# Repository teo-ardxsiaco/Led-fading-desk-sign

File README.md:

# Led-fading-desk-sign
This project started as a heartfelt, custom-made desk gift for my girlfriend, using an LM358, not rail-to-rail.
The signal, generated by a Schmitt Trigger, can be sampled as integrated between the capacitor and the upper resistance of the configuration, to be carried to the base of the TIP122 and obtain the fading.

PCB final result:

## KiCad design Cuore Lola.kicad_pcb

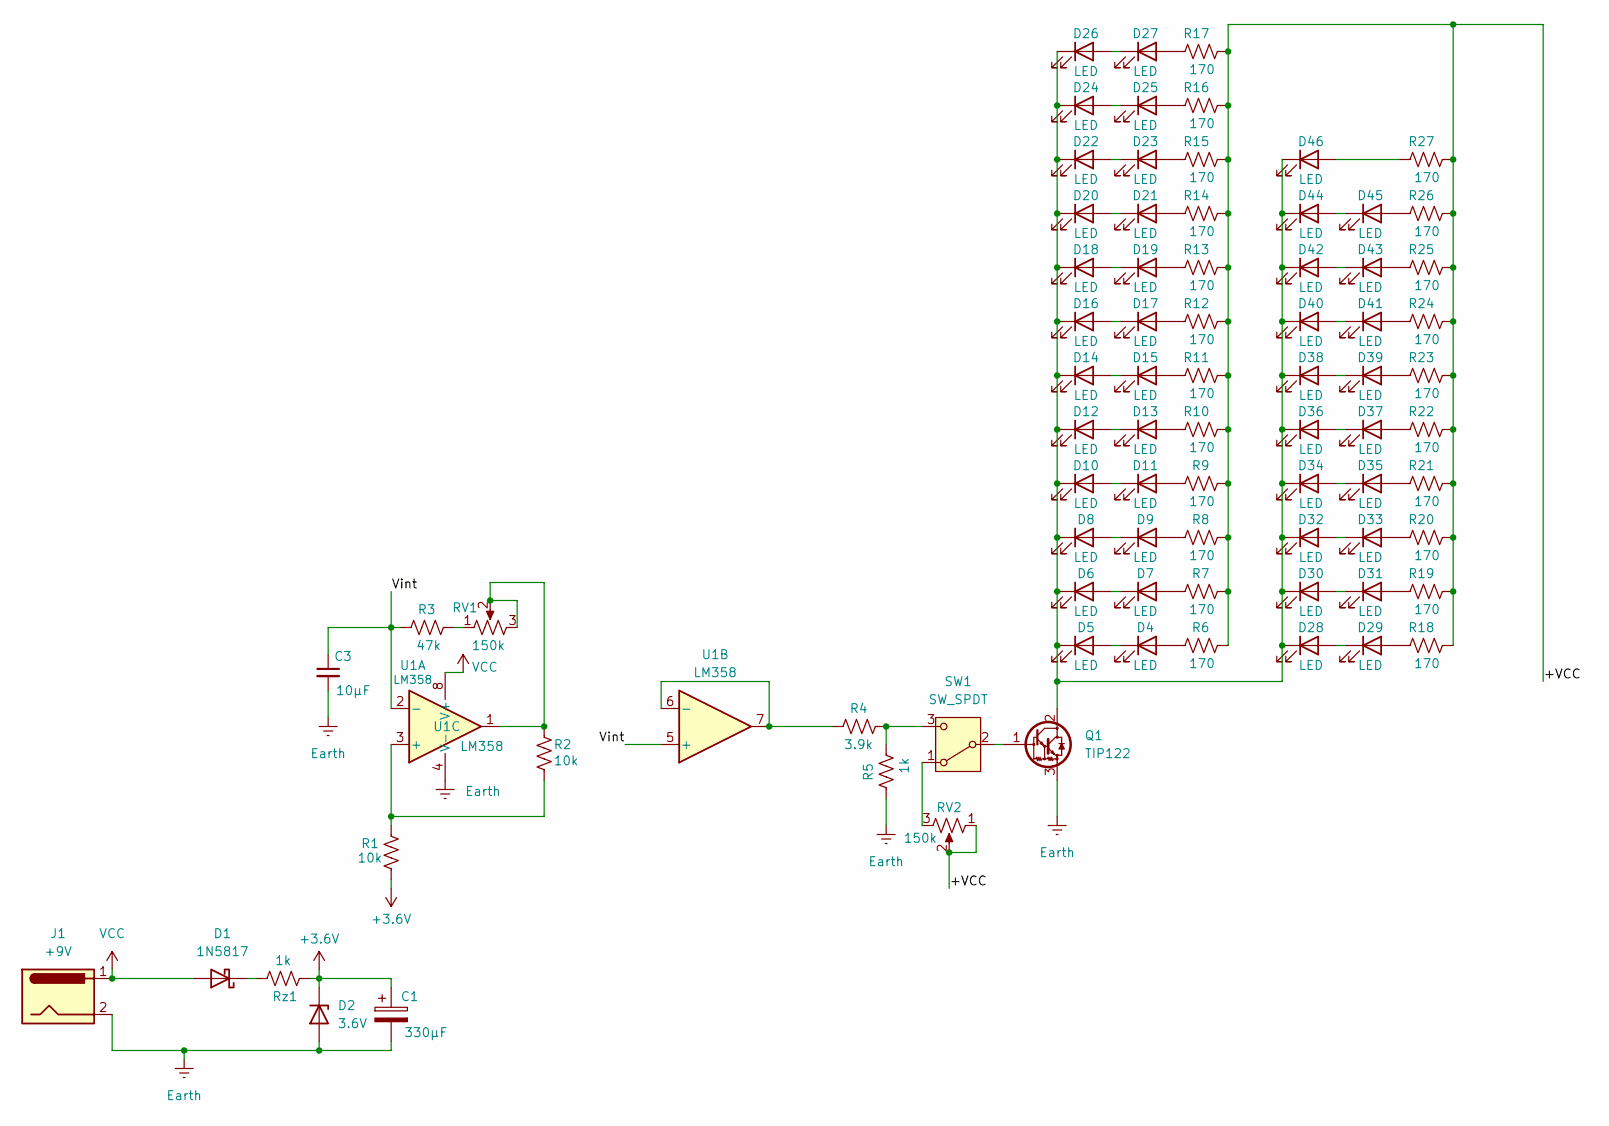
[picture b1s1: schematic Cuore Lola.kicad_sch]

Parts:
C1: 330μF; C_Radial_D8.0mm_H11.5mm_P3.50mm
C3: 10μF; C_Radial_D6.3mm_H11.0mm_P2.50mm
D1: 1N5817; D_T-1_P10.16mm_Horizontal
D2: 3.6V; D_DO-34_SOD68_P7.62mm_Horizontal
D4, D5, D6, D7, D8, D9, D10, D11, D12, D13, D14, D15, D16, D17, D18, D19, D20, D21, D22, D23, D24, D25, D26, D27, D28, D29, D30, D31, D32, D33, D34, D35, D36, D37, D38, D39, D40, D41, D42, D43, D44, D45, D46: LED; LED_D10.0mm
J1: +9V; BarrelJack_GCT_DCJ200-10-A_Horizontal
Q1: TIP122; TO-220-3_Vertical
R1, R2: 10k; R_Axial_DIN0204_L3.6mm_D1.6mm_P7.62mm_Horizontal
R3: 47k; R_Axial_DIN0204_L3.6mm_D1.6mm_P7.62mm_Horizontal
R4: 3.9k; R_Axial_DIN0204_L3.6mm_D1.6mm_P7.62mm_Horizontal
R5: 1k; R_Axial_DIN0204_L3.6mm_D1.6mm_P7.62mm_Horizontal
R6, R7, R8, R9, R10, R11, R12, R13, R14, R15, R16, R17, R18, R19, R20, R21, R22, R23, R24, R25, R26, R27: 170; R_Axial_DIN0204_L3.6mm_D1.6mm_P7.62mm_Horizontal
RV1, RV2: 150k; Potentiometer_Piher_PT-10-V10_Vertical
Rz1: 1k; R_Axial_DIN0204_L3.6mm_D1.6mm_P7.62mm_Horizontal
SW1: SW_SPDT; SW_Slide-03_Wuerth-WS-SLTV_10x2.5x6.4_P2.54mm
U1: LM358; DIP-8_W7.62mm_Socket_LongPads

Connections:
+3.6V: C1.1, D2.1 (K), R1.1, Rz1.2
/+VCC: R6.1, R7.1, R8.1, R9.1, R10.1, R11.1, R12.1, R13.1, R14.1, R15.1, R16.1, R17.1, R18.1, R19.1, R20.1, R21.1, R22.1, R23.1, R24.1, R25.1, R26.1, R27.1, RV2.1, RV2.2
/Vint: C3.1, R3.2, U1.2 (-), U1.5 (+)
Earth: C1.2, C3.2, D2.2 (A), J1.2, Q1.3 (E), R5.2, U1.4 (V-)
unnamed: D1.1 (K), Rz1.1
unnamed: D4.2 (A), R6.2
unnamed: D4.1 (K), D5.2 (A)
unnamed: D6.2 (A), D7.1 (K)
unnamed: D7.2 (A), R7.2
unnamed: D8.2 (A), D9.1 (K)
unnamed: D9.2 (A), R8.2
unnamed: D10.2 (A), D11.1 (K)
unnamed: D5.1 (K), D6.1 (K), D8.1 (K), D10.1 (K), D12.1 (K), D14.1 (K), D16.1 (K), D18.1 (K), D20.1 (K), D22.1 (K), D24.1 (K), D26.1 (K), D28.1 (K), D30.1 (K), D32.1 (K), D34.1 (K), D36.1 (K), D38.1 (K), D40.1 (K), D42.1 (K), D44.1 (K), D46.1 (K), Q1.2 (C)
unnamed: D11.2 (A), R9.2
unnamed: D12.2 (A), D13.1 (K)
unnamed: D13.2 (A), R10.2
unnamed: D14.2 (A), D15.1 (K)
unnamed: D15.2 (A), R11.2
unnamed: D16.2 (A), D17.1 (K)
unnamed: D17.2 (A), R12.2
unnamed: D18.2 (A), D19.1 (K)
unnamed: D19.2 (A), R13.2
unnamed: D20.2 (A), D21.1 (K)
unnamed: D21.2 (A), R14.2
unnamed: D22.2 (A), D23.1 (K)
unnamed: D23.2 (A), R15.2
unnamed: D24.2 (A), D25.1 (K)
unnamed: D25.2 (A), R16.2
unnamed: D26.2 (A), D27.1 (K)
unnamed: D27.2 (A), R17.2
unnamed: D28.2 (A), D29.1 (K)
unnamed: D29.2 (A), R18.2
unnamed: D30.2 (A), D31.1 (K)
unnamed: D31.2 (A), R19.2
unnamed: D32.2 (A), D33.1 (K)
unnamed: D33.2 (A), R20.2
unnamed: D34.2 (A), D35.1 (K)
unnamed: D35.2 (A), R21.2
unnamed: D36.2 (A), D37.1 (K)
unnamed: D37.2 (A), R22.2
unnamed: D38.2 (A), D39.1 (K)
unnamed: D39.2 (A), R23.2
unnamed: D40.2 (A), D41.1 (K)
unnamed: D41.2 (A), R24.2
unnamed: D42.2 (A), D43.1 (K)
unnamed: D43.2 (A), R25.2
unnamed: D44.2 (A), D45.1 (K)
unnamed: D45.2 (A), R26.2
unnamed: D46.2 (A), R27.2
unnamed: Q1.1 (B), SW1.2 (B)
unnamed: R2.2, RV1.2, RV1.3, U1.1
unnamed: R3.1, RV1.1
unnamed: RV2.3, SW1.1 (A)
unnamed: R4.1, R5.1, SW1.3 (C)
unnamed: R1.2, R2.1, U1.3 (+)
unnamed: R4.2, U1.6 (-), U1.7
VCC: D1.2 (A), J1.1, U1.8 (V+)

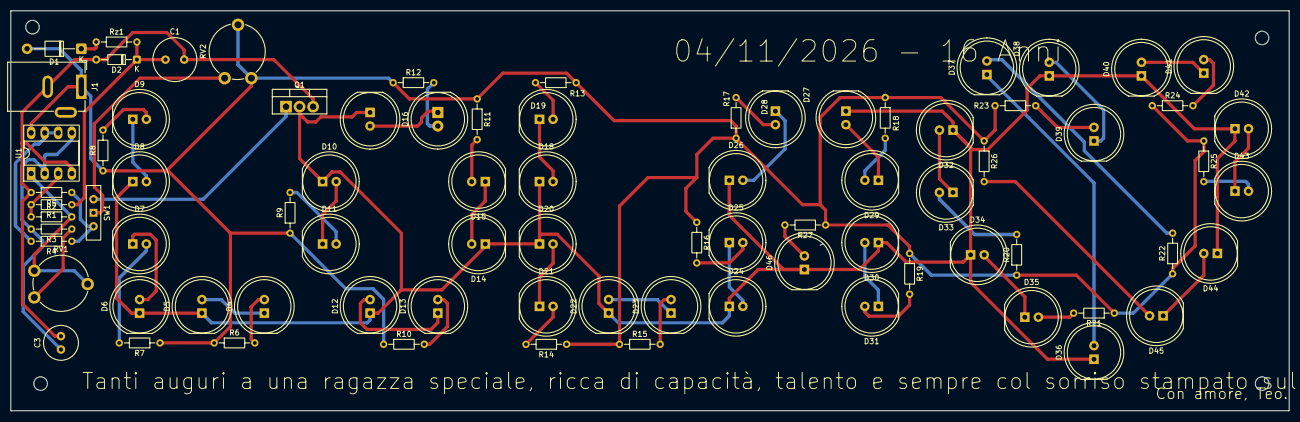
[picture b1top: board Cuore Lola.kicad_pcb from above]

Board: 2 copper layers, 239.5 x 74.9 mm, 81 parts (0 on the bottom side), 57 nets.
